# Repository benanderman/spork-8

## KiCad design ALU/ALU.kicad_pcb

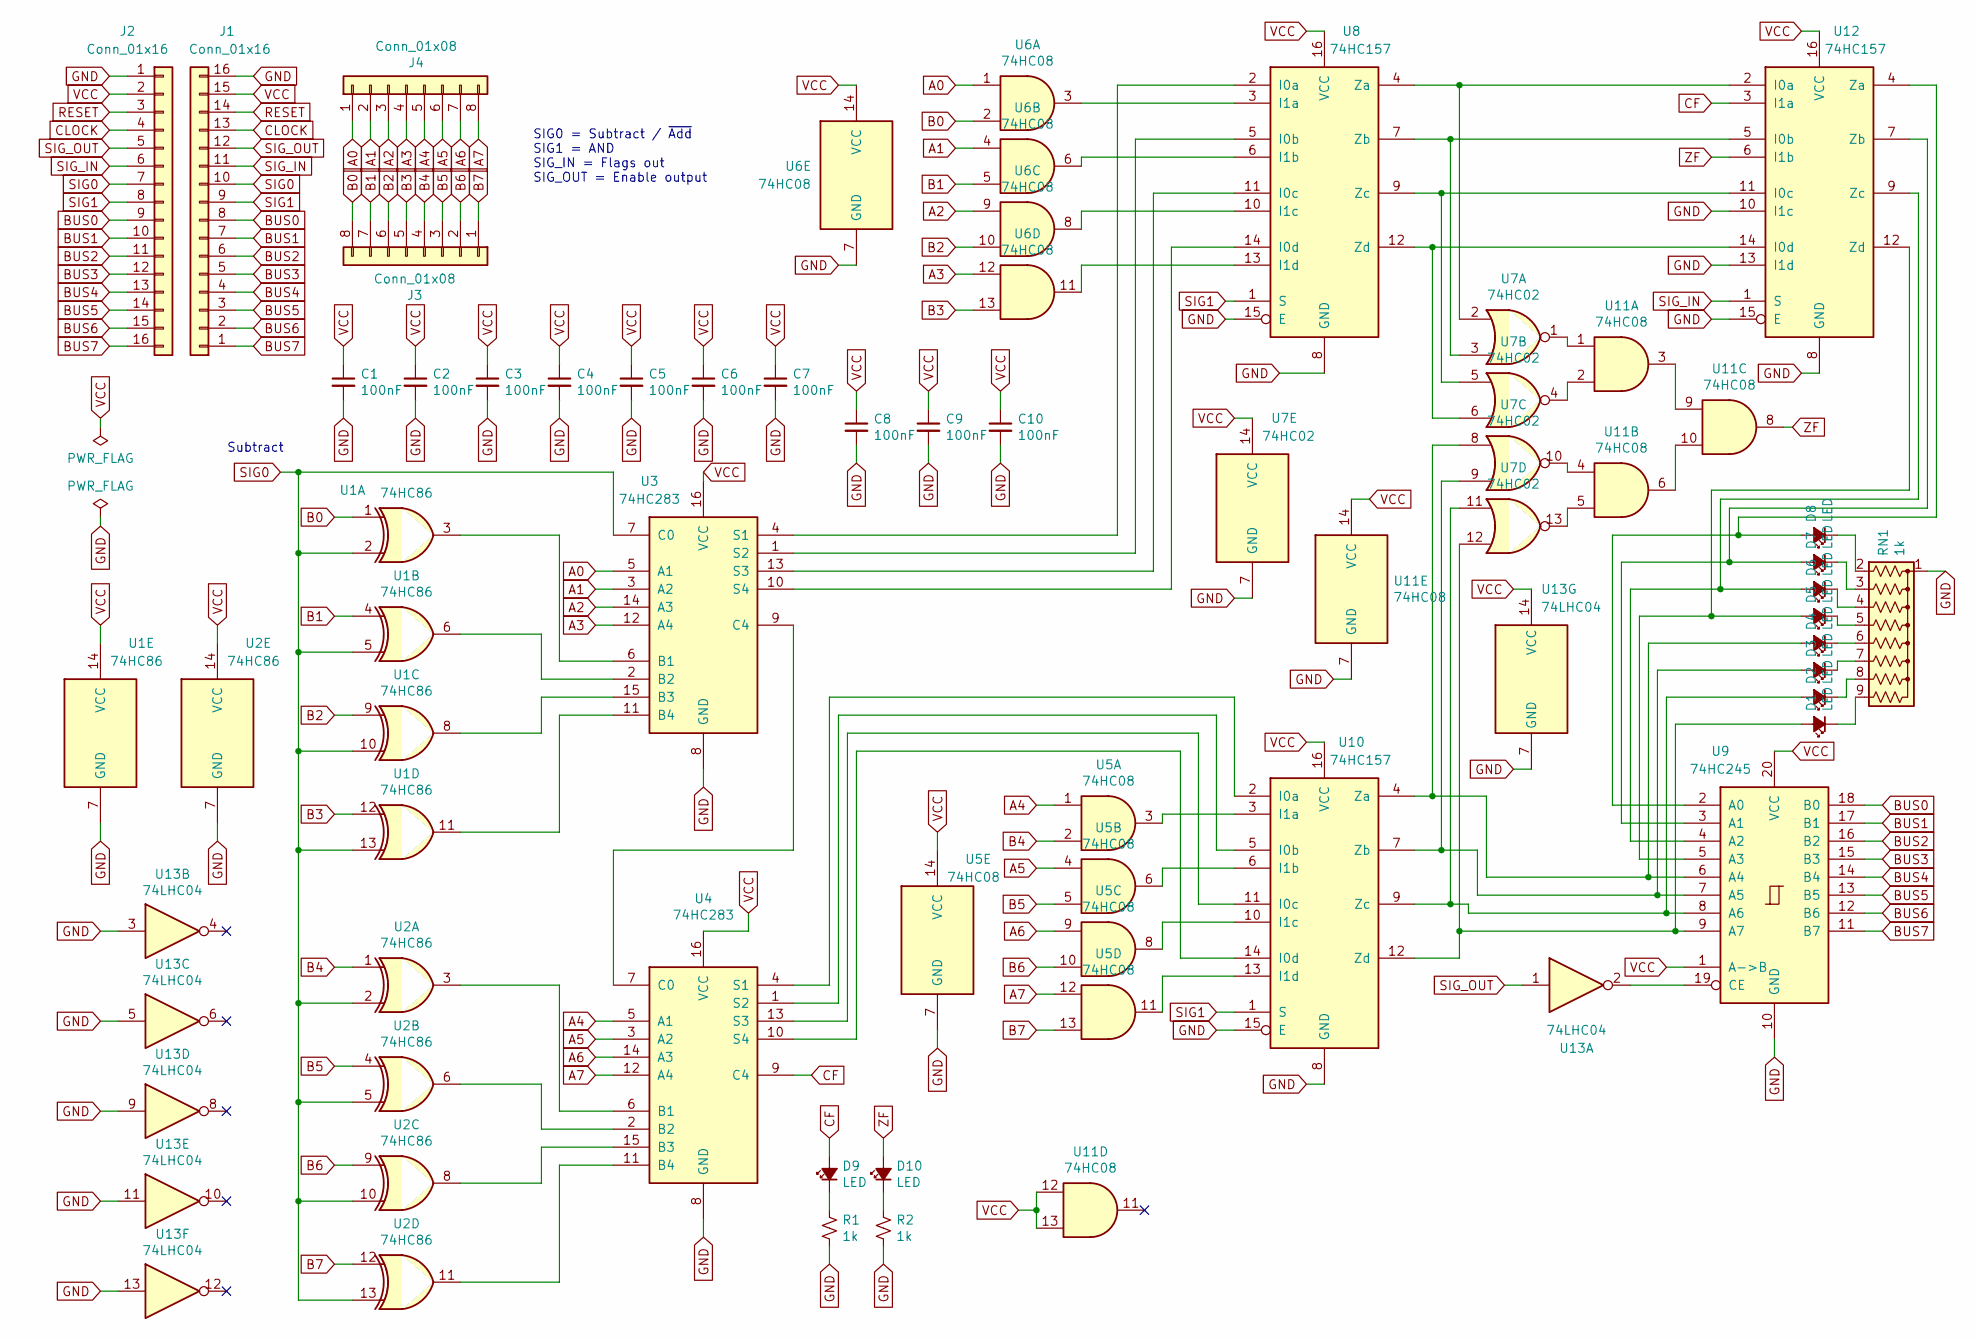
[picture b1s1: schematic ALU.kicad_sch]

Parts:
C1, C2, C3, C4, C5, C6, C7, C8, C9, C10: 100nF; C_Disc_D4.3mm_W1.9mm_P5.00mm
D1, D2, D3, D4, D5, D6, D7, D8, D9, D10: LED; LED_D3.0mm_Clear
J1, J2: Conn_01x16; PinHeader_1x16_P2.54mm_Horizontal
J3, J4: Conn_01x08; PinHeader_1x08_P2.54mm_Horizontal
R1, R2: 1k; R_Axial_DIN0207_L6.3mm_D2.5mm_P7.62mm_Horizontal
RN1: 1k; R_Array_SIP9
U1, U2: 74HC86; DIP-14_W7.62mm
U3, U4: 74HC283; DIP-16_W7.62mm
U5, U6, U11: 74HC08; DIP-14_W7.62mm
U7: 74HC02; DIP-14_W7.62mm
U8, U10, U12: 74HC157; DIP-16_W7.62mm
U9: 74HC245; DIP-20_W7.62mm
U13: 74LHC04; DIP-14_W7.62mm

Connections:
A0: J4.1, U3.5 (A1), U6.1
A1: J4.2, U3.3 (A2), U6.4
A2: J4.3, U3.14 (A3), U6.9
A3: J4.4, U3.12 (A4), U6.12
A4: J4.5, U4.5 (A1), U5.1
A5: J4.6, U4.3 (A2), U5.4
A6: J4.7, U4.14 (A3), U5.9
A7: J4.8, U4.12 (A4), U5.12
B0: J3.8, U1.1, U6.2
B1: J3.7, U1.4, U6.5
B2: J3.6, U1.9, U6.10
B3: J3.5, U1.12, U6.13
B4: J3.4, U2.1, U5.2
B5: J3.3, U2.4, U5.5
B6: J3.2, U2.9, U5.10
B7: J3.1, U2.12, U5.13
BUS0: J1.8, J2.9, U9.18 (B0)
BUS1: J1.7, J2.10, U9.17 (B1)
BUS2: J1.6, J2.11, U9.16 (B2)
BUS3: J1.5, J2.12, U9.15 (B3)
BUS4: J1.4, J2.13, U9.14 (B4)
BUS5: J1.3, J2.14, U9.13 (B5)
BUS6: J1.2, J2.15, U9.12 (B6)
BUS7: J1.1, J2.16, U9.11 (B7)
CF: D9.2 (A), U4.9 (C4), U12.3 (I1a)
CLOCK: J1.13, J2.4
GND: C1.2, C2.2, C3.2, C4.2, C5.2, C6.2, C7.2, C8.2, C9.2, C10.2, J1.16, J2.1, R1.2, R2.2, RN1.1 (common), U1.7 (GND), U2.7 (GND), U3.8 (GND), U4.8 (GND), U5.7 (GND), U6.7 (GND), U7.7 (GND), U8.8 (GND), U8.15 (E), U9.10 (GND), U10.8 (GND), U10.15 (E), U11.7 (GND), U12.8 (GND), U12.10 (I1c), U12.13 (I1d), U12.15 (E), U13.3, U13.5, U13.7 (GND), U13.9, U13.11, U13.13
unnamed: D1.2 (A), U7.12, U9.9 (A7), U10.12 (Zd)
unnamed: D1.1 (K), RN1.9 (R8)
unnamed: D2.2 (A), U7.11, U9.8 (A6), U10.9 (Zc)
unnamed: D2.1 (K), RN1.8 (R7)
unnamed: D3.2 (A), U7.9, U9.7 (A5), U10.7 (Zb)
unnamed: D3.1 (K), RN1.7 (R6)
unnamed: D4.2 (A), U7.8, U9.6 (A4), U10.4 (Za)
unnamed: D4.1 (K), RN1.6 (R5)
unnamed: D5.2 (A), U9.5 (A3), U12.12 (Zd)
unnamed: D5.1 (K), RN1.5 (R4)
unnamed: D6.2 (A), U9.4 (A2), U12.9 (Zc)
unnamed: D6.1 (K), RN1.4 (R3)
unnamed: D7.2 (A), U9.3 (A1), U12.7 (Zb)
unnamed: D7.1 (K), RN1.3 (R2)
unnamed: D8.2 (A), U9.2 (A0), U12.4 (Za)
unnamed: D8.1 (K), RN1.2 (R1)
unnamed: D9.1 (K), R1.1
unnamed: D10.1 (K), R2.1
unnamed: U1.3, U3.6 (B1)
unnamed: U1.6, U3.2 (B2)
unnamed: U1.8, U3.15 (B3)
unnamed: U1.11, U3.11 (B4)
unnamed: U3.9 (C4), U4.7 (C0)
unnamed: U3.4 (S1), U8.2 (I0a)
unnamed: U3.1 (S2), U8.5 (I0b)
unnamed: U3.13 (S3), U8.11 (I0c)
unnamed: U3.10 (S4), U8.14 (I0d)
unnamed: U2.3, U4.6 (B1)
unnamed: U2.6, U4.2 (B2)
unnamed: U2.8, U4.15 (B3)
unnamed: U2.11, U4.11 (B4)
unnamed: U6.3, U8.3 (I1a)
unnamed: U6.6, U8.6 (I1b)
unnamed: U6.8, U8.10 (I1c)
unnamed: U6.11, U8.13 (I1d)
unnamed: U9.19 (CE), U13.2
unnamed: U4.4 (S1), U10.2 (I0a)
unnamed: U4.1 (S2), U10.5 (I0b)
unnamed: U4.13 (S3), U10.11 (I0c)
unnamed: U4.10 (S4), U10.14 (I0d)
unnamed: U5.3, U10.3 (I1a)
unnamed: U5.6, U10.6 (I1b)
unnamed: U5.8, U10.10 (I1c)
unnamed: U5.11, U10.13 (I1d)
unnamed: U7.1, U11.1
unnamed: U7.4, U11.2
unnamed: U11.3, U11.9
unnamed: U7.10, U11.4
unnamed: U7.13, U11.5
unnamed: U11.6, U11.10
unnamed: U7.2, U8.4 (Za), U12.2 (I0a)
unnamed: U7.3, U8.7 (Zb), U12.5 (I0b)
unnamed: U7.5, U8.9 (Zc), U12.11 (I0c)
unnamed: U7.6, U8.12 (Zd), U12.14 (I0d)
RESET: J1.14, J2.3
SIG0: J1.10, J2.7, U1.2, U1.5, U1.10, U1.13, U2.2, U2.5, U2.10, U2.13, U3.7 (C0)
SIG1: J1.9, J2.8, U8.1 (S), U10.1 (S)
SIG_IN: J1.11, J2.6, U12.1 (S)
SIG_OUT: J1.12, J2.5, U13.1
VCC: C1.1, C2.1, C3.1, C4.1, C5.1, C6.1, C7.1, C8.1, C9.1, C10.1, J1.15, J2.2, U1.14 (VCC), U2.14 (VCC), U3.16 (VCC), U4.16 (VCC), U5.14 (VCC), U6.14 (VCC), U7.14 (VCC), U8.16 (VCC), U9.1 (A->B), U9.20 (VCC), U10.16 (VCC), U11.12, U11.13, U11.14 (VCC), U12.16 (VCC), U13.14 (VCC)
ZF: D10.2 (A), U11.8, U12.6 (I1b)

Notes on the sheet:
Subtract
SIG0 = Subtract / ~{Add} SIG1 = AND SIG_IN = Flags out SIG_OUT = Enable output

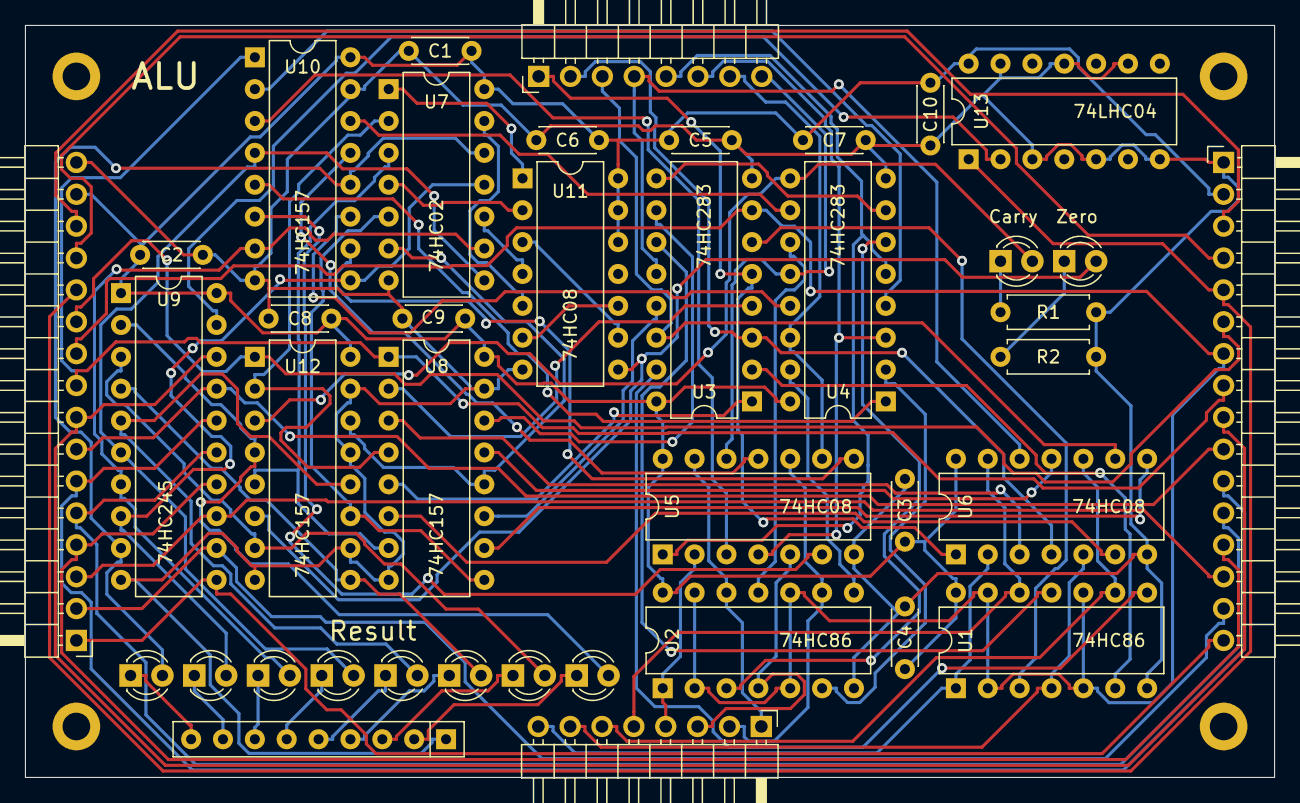
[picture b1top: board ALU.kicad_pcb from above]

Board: 2 copper layers, 99.6 x 59.9 mm, 44 parts (0 on the bottom side), 88 nets.

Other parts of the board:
HOLE1, HOLE2, HOLE3, HOLE4: MountingHole_2.2mm_M2_DIN965_Pad

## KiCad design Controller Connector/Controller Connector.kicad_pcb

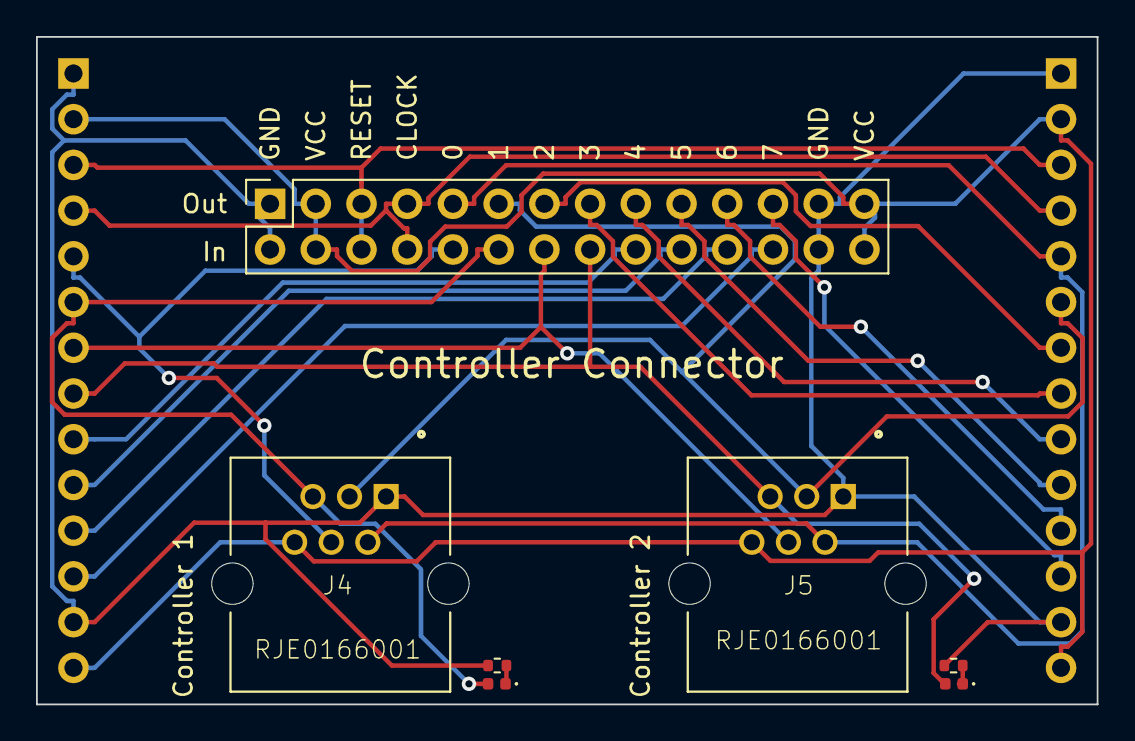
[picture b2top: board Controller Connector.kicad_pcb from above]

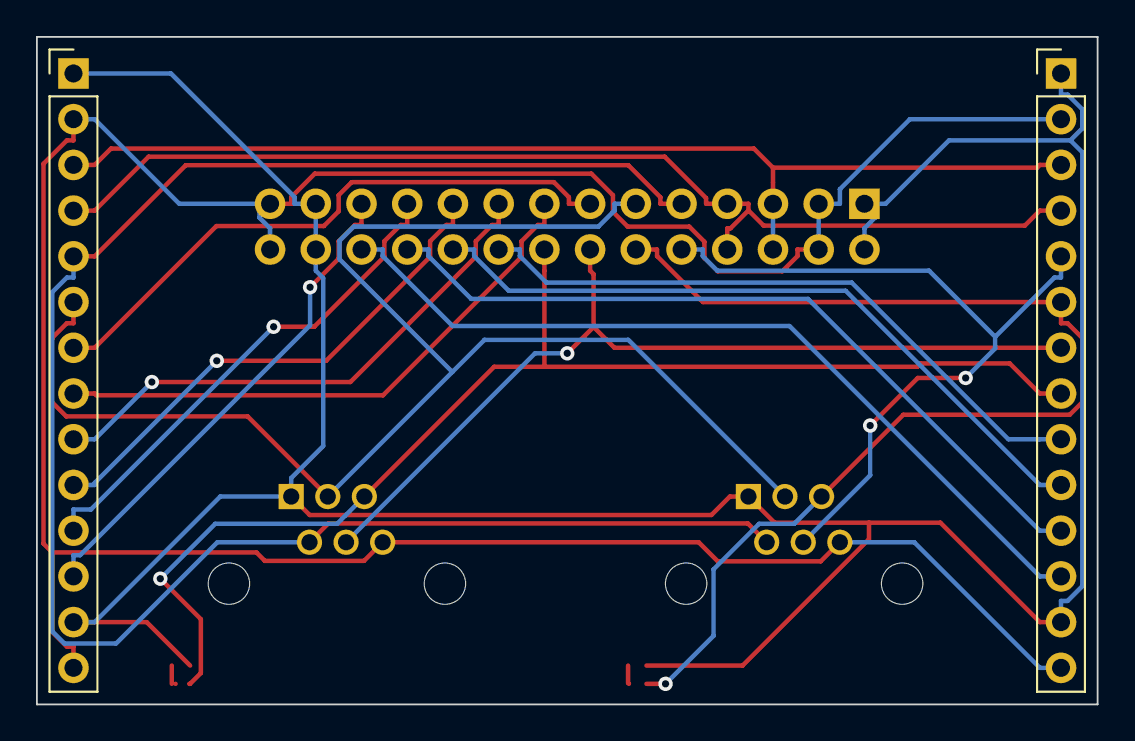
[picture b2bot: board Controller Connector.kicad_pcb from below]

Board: 2 copper layers, 58.9 x 37.1 mm, 9 parts (2 on the bottom side), 22 nets.

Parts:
D1, D2: LED; LED_0402_1005Metric
J1, J2: Conn_01x14; PinHeader_1x14_P2.54mm_Vertical
J3: Conn_02x14_Top_Bottom; PinSocket_2x14_P2.54mm_Vertical
J4, J5: RJE0166001; Connfly_RJ12_DS1133-S60BPX
R1, R2: 10k; R_0402_1005Metric

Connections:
CLOCK: J1.4, J2.4, J3.7, J3.8
GND: J1.1, J1.13, J2.1, J2.13, J3.1, J3.2, J3.25, J3.26, J4.1, J5.1, R1.2, R2.2
IN0: J2.5, J3.10, J4.4
IN1: D1.2 (A), J2.6, J3.12, J4.5
IN2: J2.7, J3.14, J5.4
IN3: D2.2 (A), J2.8, J3.16, J5.5
IN4: J2.9, J3.18
IN5: J2.10, J3.20
IN6: J2.11, J3.22
IN7: J2.12, J3.24
unnamed: D1.1 (K), R1.1
unnamed: D2.1 (K), R2.1
OUT0: J1.5, J3.9, J4.2, J5.2
OUT1: J1.6, J3.11, J4.3, J5.3
OUT2: J1.7, J3.13
OUT3: J1.8, J3.15
OUT4: J1.9, J3.17
OUT5: J1.10, J3.19
OUT6: J1.11, J3.21
OUT7: J1.12, J3.23
RESET: J1.3, J2.3, J3.5, J3.6
VCC: J1.2, J1.14, J2.2, J2.14, J3.3, J3.4, J3.27, J3.28, J4.6, J5.6

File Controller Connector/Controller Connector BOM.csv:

Designator,Comment,Footprint,LCSC Part Number
"D1, D2",LED,LED_0402_1005Metric,C965793
"J1, J2",Conn_01x14,Connector_Generic:Conn_01x14,
J3,Conn_02x14_Top_Bottom,Connector_Generic:Conn_02x14_Odd_Even,
"J4, J5",RJE0166001,RJE0166001-RJE0166001,C77859
"R1, R2",10k,R_0402_1005Metric,C25744

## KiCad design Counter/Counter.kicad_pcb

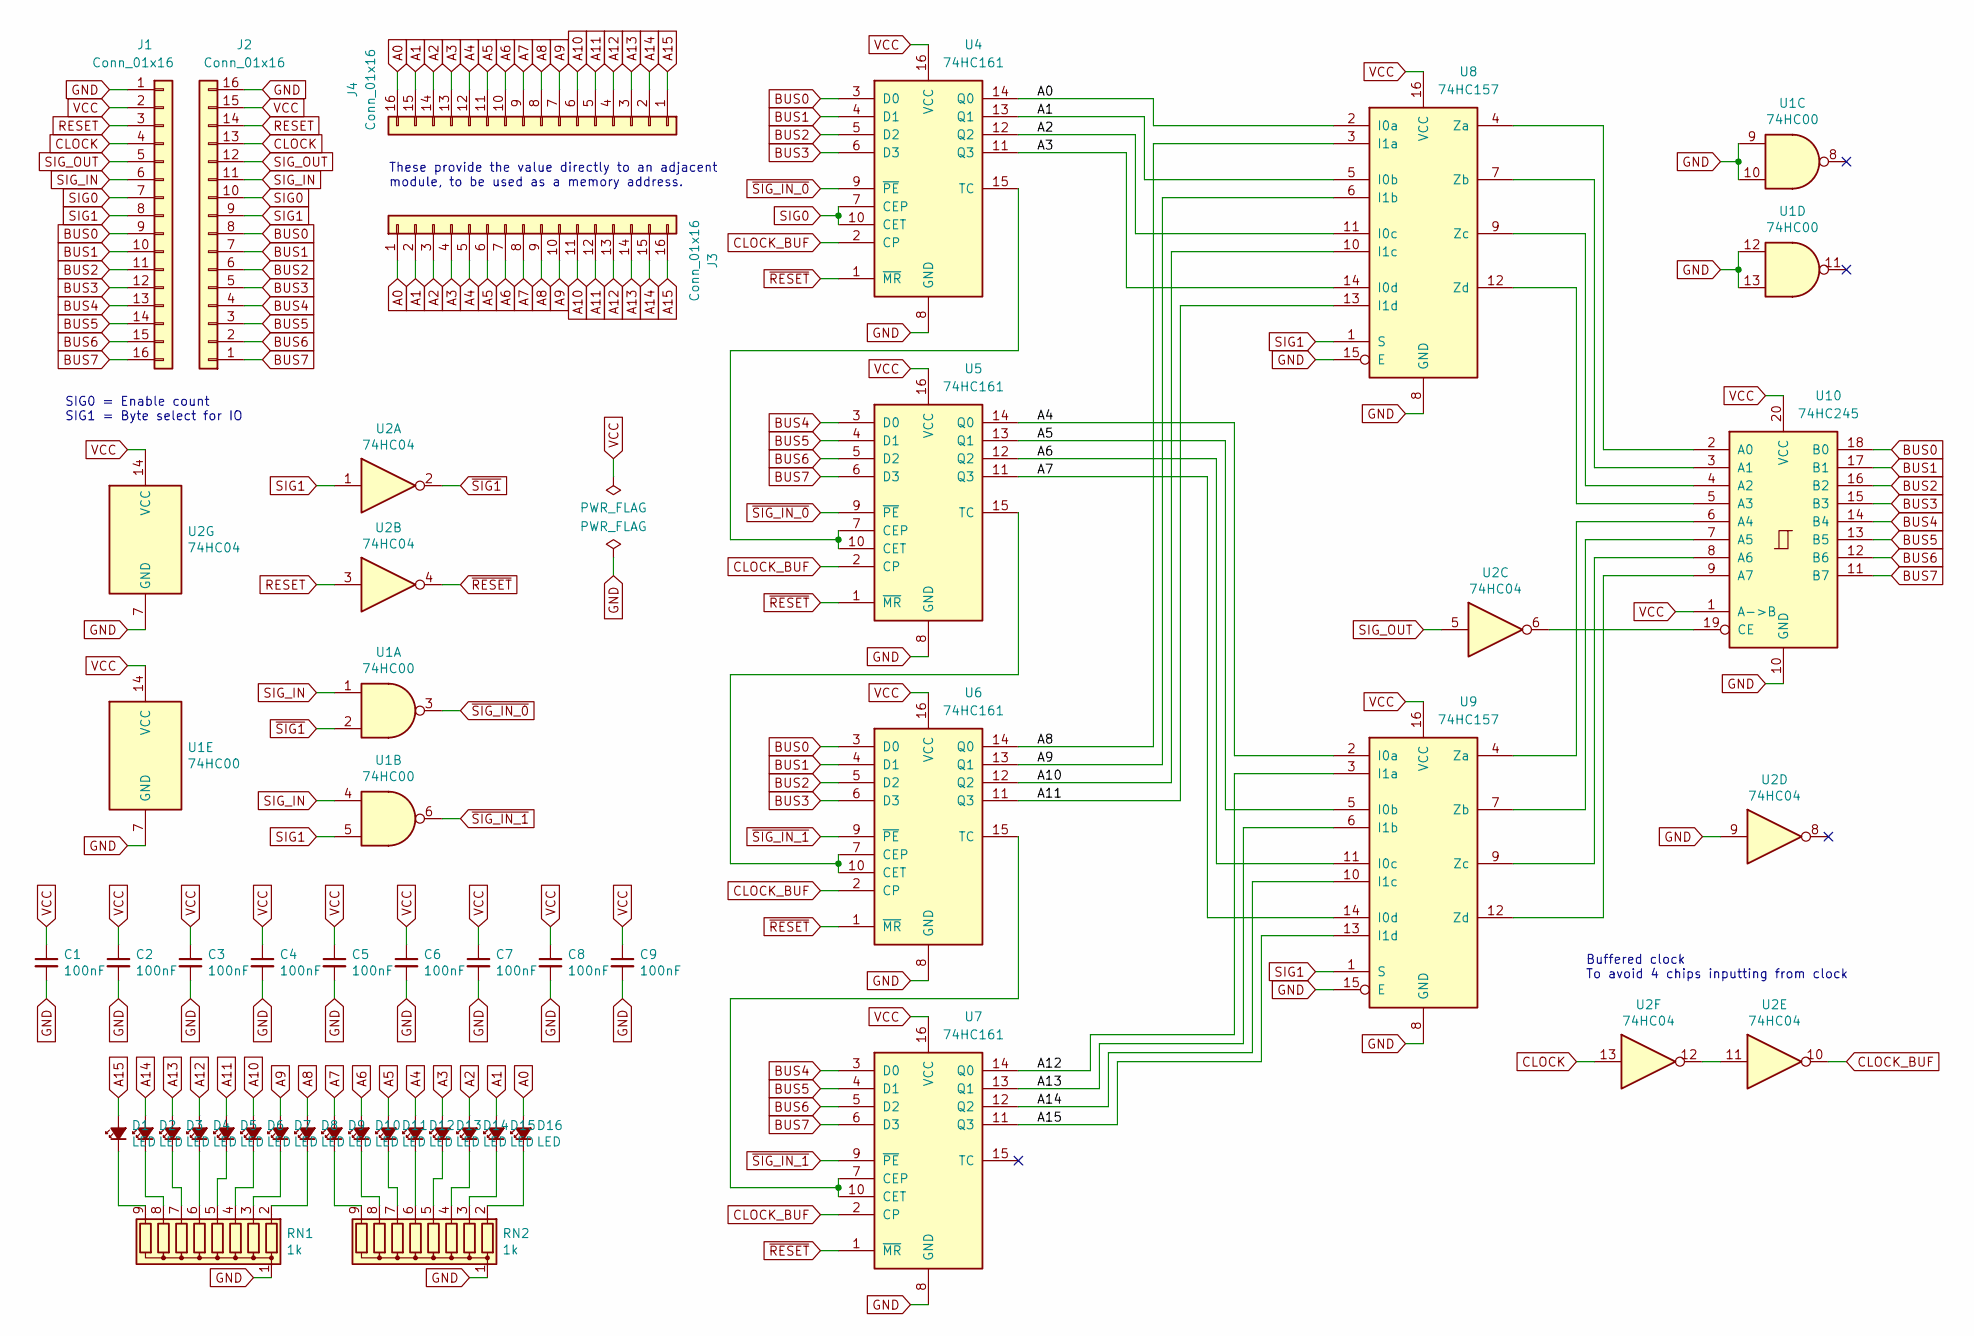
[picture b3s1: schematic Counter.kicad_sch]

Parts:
C1, C2, C3, C4, C5, C6, C7, C8, C9: 100nF; C_Disc_D4.3mm_W1.9mm_P5.00mm
D1, D2, D3, D4, D5, D6, D7, D8, D9, D10, D11, D12, D13, D14, D15, D16: LED; LED_D3.0mm
J1, J2: Conn_01x16; PinHeader_1x16_P2.54mm_Horizontal
J3, J4: Conn_01x16; PinSocket_1x16_P2.54mm_Horizontal
RN1, RN2: 1k; R_Array_SIP9
U1: 74HC00; DIP-14_W7.62mm
U2: 74HC04; DIP-14_W7.62mm
U4, U5, U6, U7: 74HC161; DIP-16_W7.62mm
U8, U9: 74HC157; DIP-16_W7.62mm
U10: 74HC245; DIP-20_W7.62mm

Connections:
A0: D16.2 (A), J3.1, J4.16, U4.14 (Q0), U8.2 (I0a)
A1: D15.2 (A), J3.2, J4.15, U4.13 (Q1), U8.5 (I0b)
A2: D14.2 (A), J3.3, J4.14, U4.12 (Q2), U8.11 (I0c)
A3: D13.2 (A), J3.4, J4.13, U4.11 (Q3), U8.14 (I0d)
A4: D12.2 (A), J3.5, J4.12, U5.14 (Q0), U9.2 (I0a)
A5: D11.2 (A), J3.6, J4.11, U5.13 (Q1), U9.5 (I0b)
A6: D10.2 (A), J3.7, J4.10, U5.12 (Q2), U9.11 (I0c)
A7: D9.2 (A), J3.8, J4.9, U5.11 (Q3), U9.14 (I0d)
A8: D8.2 (A), J3.9, J4.8, U6.14 (Q0), U8.3 (I1a)
A9: D7.2 (A), J3.10, J4.7, U6.13 (Q1), U8.6 (I1b)
A10: D6.2 (A), J3.11, J4.6, U6.12 (Q2), U8.10 (I1c)
A11: D5.2 (A), J3.12, J4.5, U6.11 (Q3), U8.13 (I1d)
A12: D4.2 (A), J3.13, J4.4, U7.14 (Q0), U9.3 (I1a)
A13: D3.2 (A), J3.14, J4.3, U7.13 (Q1), U9.6 (I1b)
A14: D2.2 (A), J3.15, J4.2, U7.12 (Q2), U9.10 (I1c)
A15: D1.2 (A), J3.16, J4.1, U7.11 (Q3), U9.13 (I1d)
BUS0: J1.9, J2.8, U4.3 (D0), U6.3 (D0), U10.18 (B0)
BUS1: J1.10, J2.7, U4.4 (D1), U6.4 (D1), U10.17 (B1)
BUS2: J1.11, J2.6, U4.5 (D2), U6.5 (D2), U10.16 (B2)
BUS3: J1.12, J2.5, U4.6 (D3), U6.6 (D3), U10.15 (B3)
BUS4: J1.13, J2.4, U5.3 (D0), U7.3 (D0), U10.14 (B4)
BUS5: J1.14, J2.3, U5.4 (D1), U7.4 (D1), U10.13 (B5)
BUS6: J1.15, J2.2, U5.5 (D2), U7.5 (D2), U10.12 (B6)
BUS7: J1.16, J2.1, U5.6 (D3), U7.6 (D3), U10.11 (B7)
CLOCK: J1.4, J2.13, U2.13
CLOCK_BUF: U2.10, U4.2 (CP), U5.2 (CP), U6.2 (CP), U7.2 (CP)
GND: C1.2, C2.2, C3.2, C4.2, C5.2, C6.2, C7.2, C8.2, C9.2, J1.1, J2.16, RN1.1 (common), RN2.1 (common), U1.7 (GND), U1.9, U1.10, U1.12, U1.13, U2.7 (GND), U2.9, U4.8 (GND), U5.8 (GND), U6.8 (GND), U7.8 (GND), U8.8 (GND), U8.15 (E), U9.8 (GND), U9.15 (E), U10.10 (GND)
unnamed: D1.1 (K), RN1.9 (R8)
unnamed: D2.1 (K), RN1.8 (R7)
unnamed: D3.1 (K), RN1.7 (R6)
unnamed: D4.1 (K), RN1.6 (R5)
unnamed: D5.1 (K), RN1.5 (R4)
unnamed: D6.1 (K), RN1.4 (R3)
unnamed: D7.1 (K), RN1.3 (R2)
unnamed: D8.1 (K), RN1.2 (R1)
unnamed: D9.1 (K), RN2.9 (R8)
unnamed: D10.1 (K), RN2.8 (R7)
unnamed: D11.1 (K), RN2.7 (R6)
unnamed: D12.1 (K), RN2.6 (R5)
unnamed: D13.1 (K), RN2.5 (R4)
unnamed: D14.1 (K), RN2.4 (R3)
unnamed: D15.1 (K), RN2.3 (R2)
unnamed: D16.1 (K), RN2.2 (R1)
unnamed: U2.11, U2.12
unnamed: U4.15 (TC), U5.7 (CEP), U5.10 (CET)
unnamed: U5.15 (TC), U6.7 (CEP), U6.10 (CET)
unnamed: U6.15 (TC), U7.7 (CEP), U7.10 (CET)
unnamed: U8.4 (Za), U10.2 (A0)
unnamed: U8.7 (Zb), U10.3 (A1)
unnamed: U8.9 (Zc), U10.4 (A2)
unnamed: U8.12 (Zd), U10.5 (A3)
unnamed: U9.4 (Za), U10.6 (A4)
unnamed: U9.7 (Zb), U10.7 (A5)
unnamed: U9.9 (Zc), U10.8 (A6)
unnamed: U9.12 (Zd), U10.9 (A7)
unnamed: U2.6, U10.19 (CE)
RESET: J1.3, J2.14, U2.3
SIG0: J1.7, J2.10, U4.7 (CEP), U4.10 (CET)
SIG1: J1.8, J2.9, U1.5, U2.1, U8.1 (S), U9.1 (S)
SIG_IN: J1.6, J2.11, U1.1, U1.4
SIG_OUT: J1.5, J2.12, U2.5
VCC: C1.1, C2.1, C3.1, C4.1, C5.1, C6.1, C7.1, C8.1, C9.1, J1.2, J2.15, U1.14 (VCC), U2.14 (VCC), U4.16 (VCC), U5.16 (VCC), U6.16 (VCC), U7.16 (VCC), U8.16 (VCC), U9.16 (VCC), U10.1 (A->B), U10.20 (VCC)
~RESET: U2.4, U4.1 (~MR), U5.1 (~MR), U6.1 (~MR), U7.1 (~MR)
~SIG1: U1.2, U2.2
~SIG_IN_0: U1.3, U4.9 (~PE), U5.9 (~PE)
~SIG_IN_1: U1.6, U6.9 (~PE), U7.9 (~PE)

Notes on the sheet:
Buffered clock To avoid 4 chips inputting from clock
SIG0 = Enable count SIG1 = Byte select for IO
These provide the value directly to an adjacent module, to be used as a memory address.

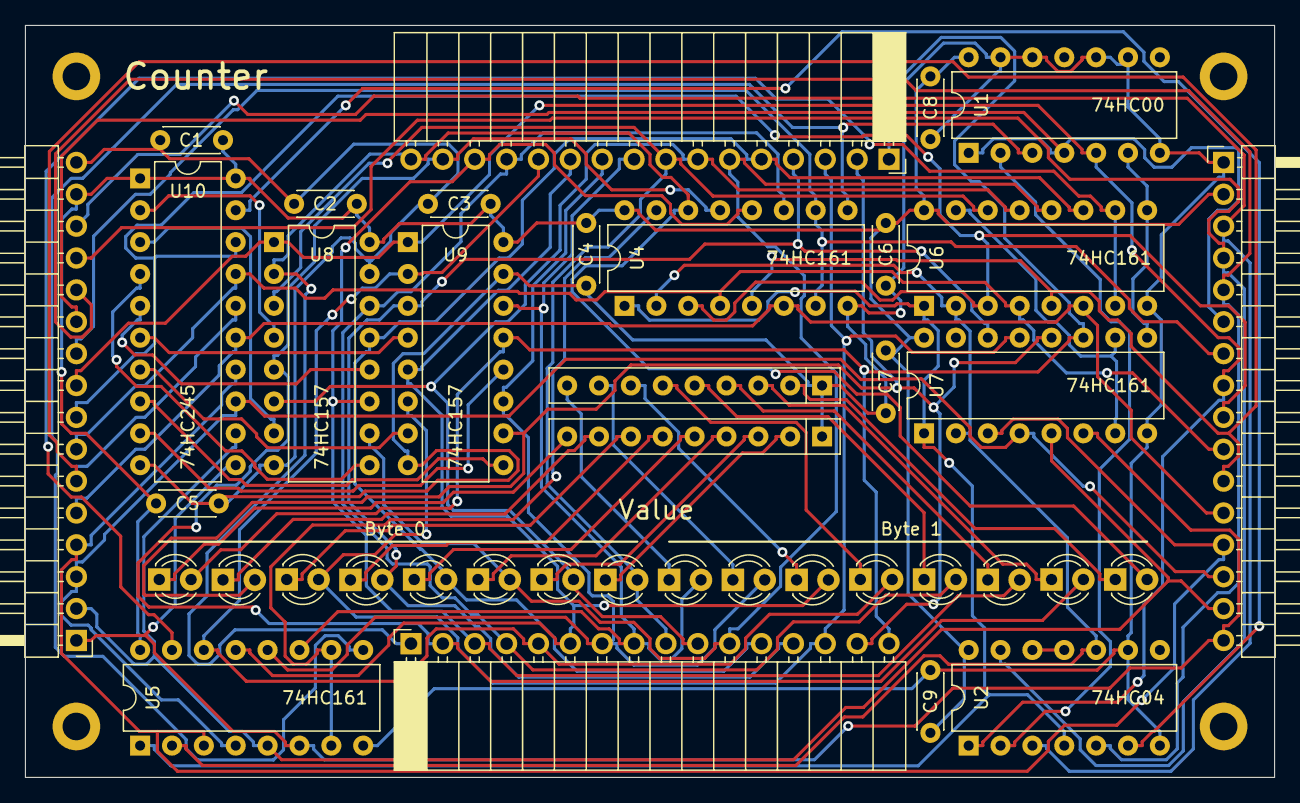
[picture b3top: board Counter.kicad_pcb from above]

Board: 2 copper layers, 99.6 x 59.9 mm, 44 parts (0 on the bottom side), 66 nets.

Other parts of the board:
HOLE1, HOLE2, HOLE3, HOLE4: MountingHole_2.2mm_M2_DIN965_Pad

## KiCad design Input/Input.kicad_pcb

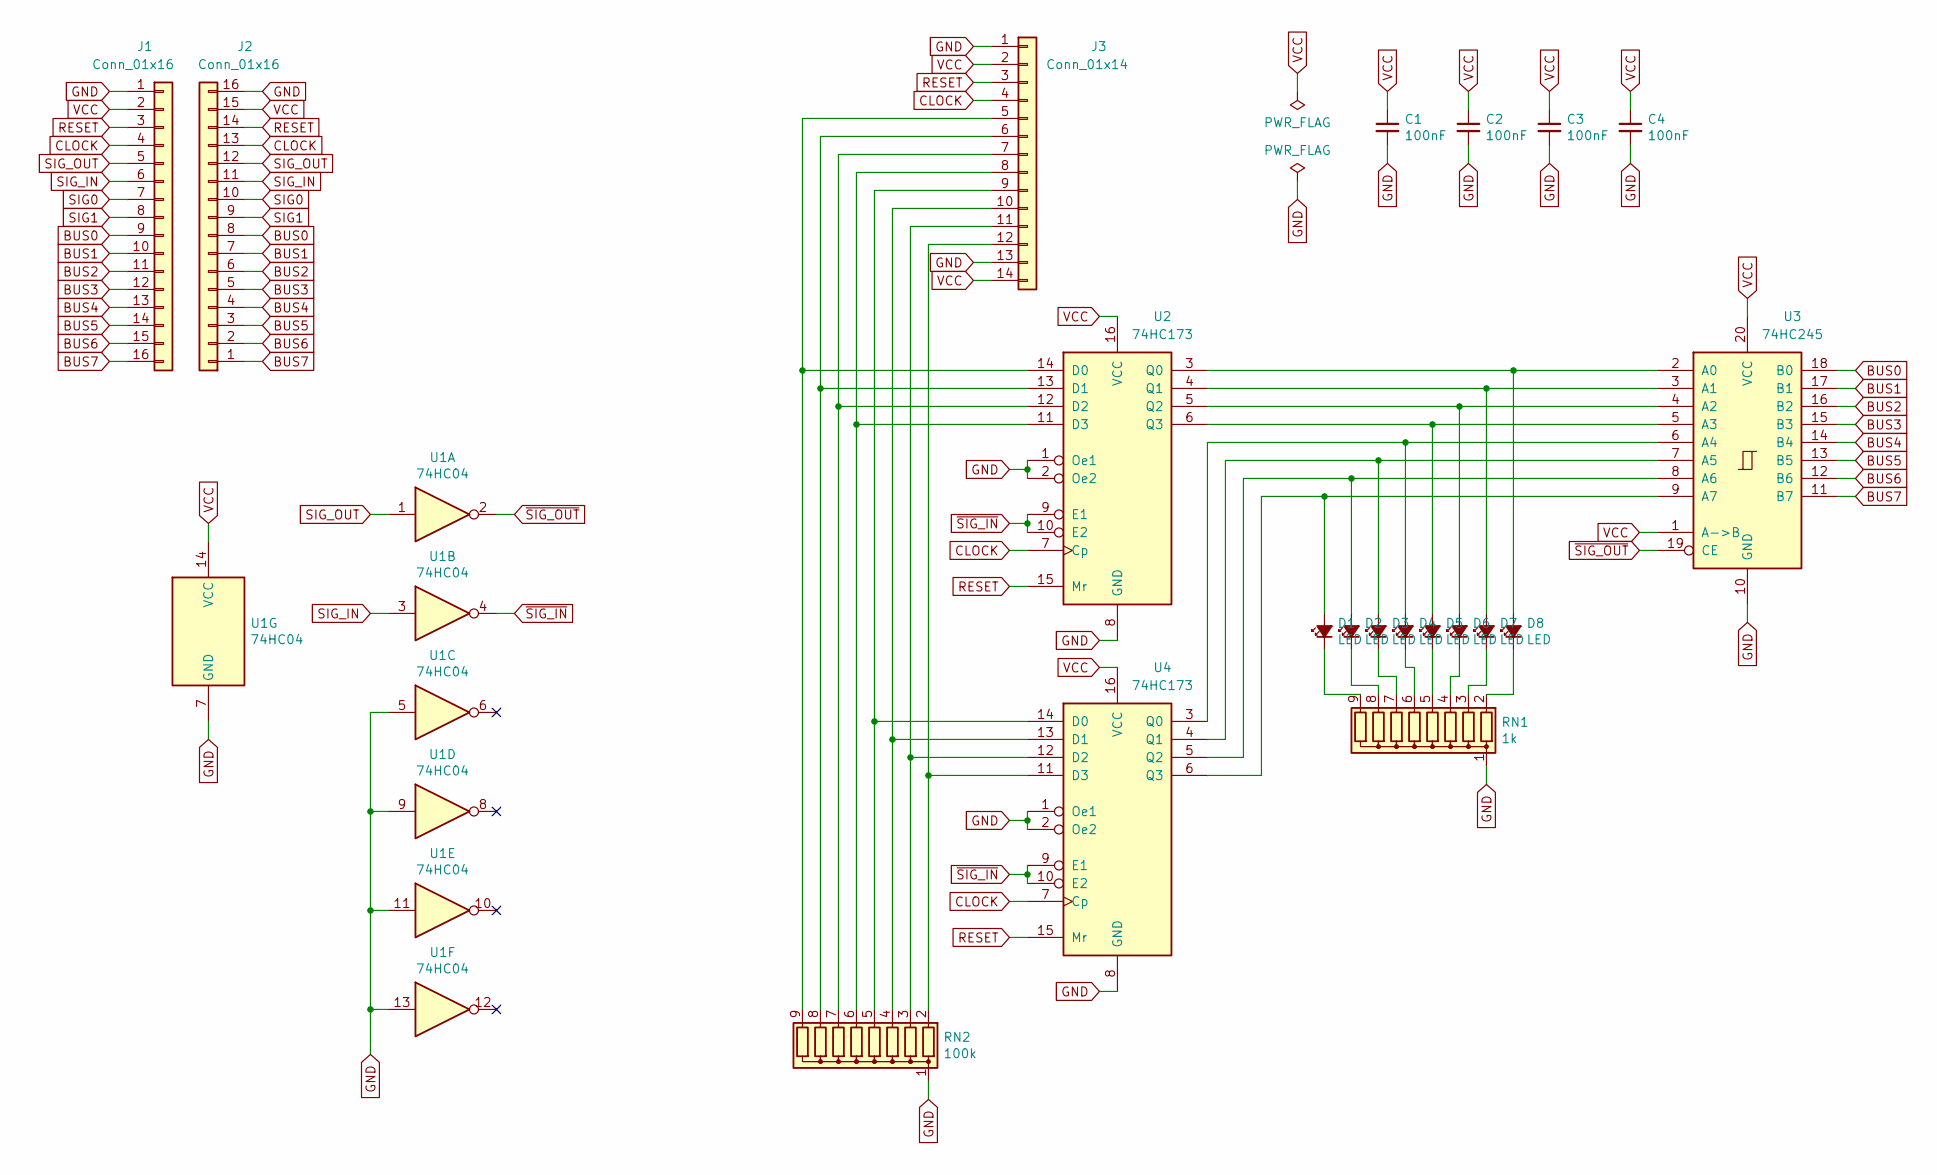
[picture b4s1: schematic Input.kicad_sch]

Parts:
C1, C2, C3, C4: 100nF; C_Disc_D4.3mm_W1.9mm_P5.00mm
D1, D2, D3, D4, D5, D6, D7, D8: LED; LED_D3.0mm_Clear
J1, J2: Conn_01x16; PinHeader_1x16_P2.54mm_Horizontal
J3: Conn_01x14; PinSocket_1x14_P2.54mm_Vertical
RN1: 1k; R_Array_SIP9
RN2: 100k; R_Array_SIP9
U1: 74HC04; DIP-14_W7.62mm
U2, U4: 74HC173; DIP-16_W7.62mm
U3: 74HC245; DIP-20_W7.62mm

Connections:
BUS0: J1.9, J2.8, U3.18 (B0)
BUS1: J1.10, J2.7, U3.17 (B1)
BUS2: J1.11, J2.6, U3.16 (B2)
BUS3: J1.12, J2.5, U3.15 (B3)
BUS4: J1.13, J2.4, U3.14 (B4)
BUS5: J1.14, J2.3, U3.13 (B5)
BUS6: J1.15, J2.2, U3.12 (B6)
BUS7: J1.16, J2.1, U3.11 (B7)
CLOCK: J1.4, J2.13, J3.4, U2.7 (Cp), U4.7 (Cp)
GND: C1.2, C2.2, C3.2, C4.2, J1.1, J2.16, J3.1, J3.13, RN1.1 (common), RN2.1 (common), U1.5, U1.7 (GND), U1.9, U1.11, U1.13, U2.1 (Oe1), U2.2 (Oe2), U2.8 (GND), U3.10 (GND), U4.1 (Oe1), U4.2 (Oe2), U4.8 (GND)
unnamed: D1.2 (A), U3.9 (A7), U4.6 (Q3)
unnamed: D1.1 (K), RN1.9 (R8)
unnamed: D2.2 (A), U3.8 (A6), U4.5 (Q2)
unnamed: D2.1 (K), RN1.8 (R7)
unnamed: D3.2 (A), U3.7 (A5), U4.4 (Q1)
unnamed: D3.1 (K), RN1.7 (R6)
unnamed: D4.2 (A), U3.6 (A4), U4.3 (Q0)
unnamed: D4.1 (K), RN1.6 (R5)
unnamed: D5.2 (A), U2.6 (Q3), U3.5 (A3)
unnamed: D5.1 (K), RN1.5 (R4)
unnamed: D6.2 (A), U2.5 (Q2), U3.4 (A2)
unnamed: D6.1 (K), RN1.4 (R3)
unnamed: D7.2 (A), U2.4 (Q1), U3.3 (A1)
unnamed: D7.1 (K), RN1.3 (R2)
unnamed: D8.2 (A), U2.3 (Q0), U3.2 (A0)
unnamed: D8.1 (K), RN1.2 (R1)
unnamed: J3.5, RN2.9 (R8), U2.14 (D0)
unnamed: J3.6, RN2.8 (R7), U2.13 (D1)
unnamed: J3.7, RN2.7 (R6), U2.12 (D2)
unnamed: J3.8, RN2.6 (R5), U2.11 (D3)
unnamed: J3.9, RN2.5 (R4), U4.14 (D0)
unnamed: J3.10, RN2.4 (R3), U4.13 (D1)
unnamed: J3.11, RN2.3 (R2), U4.12 (D2)
unnamed: J3.12, RN2.2 (R1), U4.11 (D3)
RESET: J1.3, J2.14, J3.3, U2.15 (Mr), U4.15 (Mr)
SIG0: J1.7, J2.10
SIG1: J1.8, J2.9
SIG_IN: J1.6, J2.11, U1.3
SIG_OUT: J1.5, J2.12, U1.1
VCC: C1.1, C2.1, C3.1, C4.1, J1.2, J2.15, J3.2, J3.14, U1.14 (VCC), U2.16 (VCC), U3.1 (A->B), U3.20 (VCC), U4.16 (VCC)
~SIG_IN: U1.4, U2.9 (E1), U2.10 (E2), U4.9 (E1), U4.10 (E2)
~SIG_OUT: U1.2, U3.19 (CE)

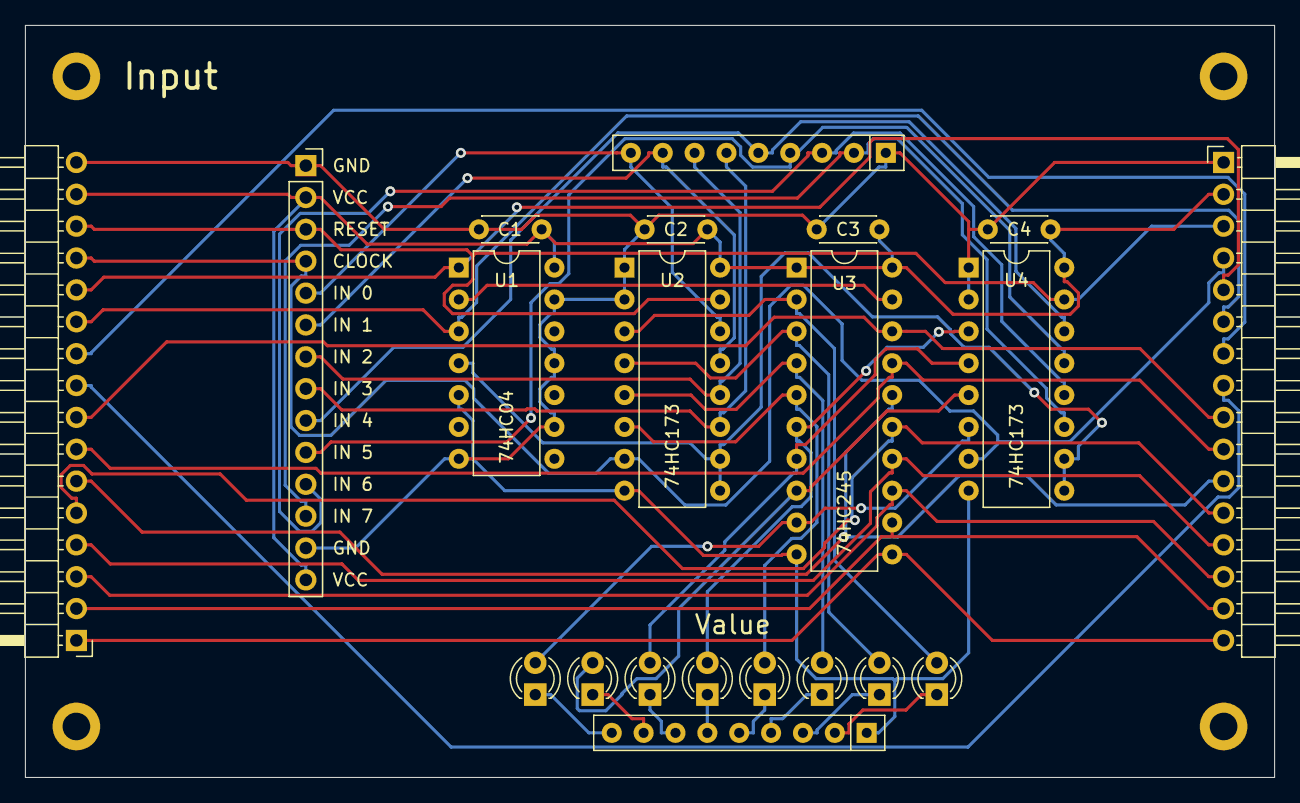
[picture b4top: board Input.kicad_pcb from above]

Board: 2 copper layers, 99.6 x 59.9 mm, 25 parts (0 on the bottom side), 42 nets.

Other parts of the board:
HOLE1, HOLE2, HOLE3, HOLE4: MountingHole_2.2mm_M2_DIN965_Pad

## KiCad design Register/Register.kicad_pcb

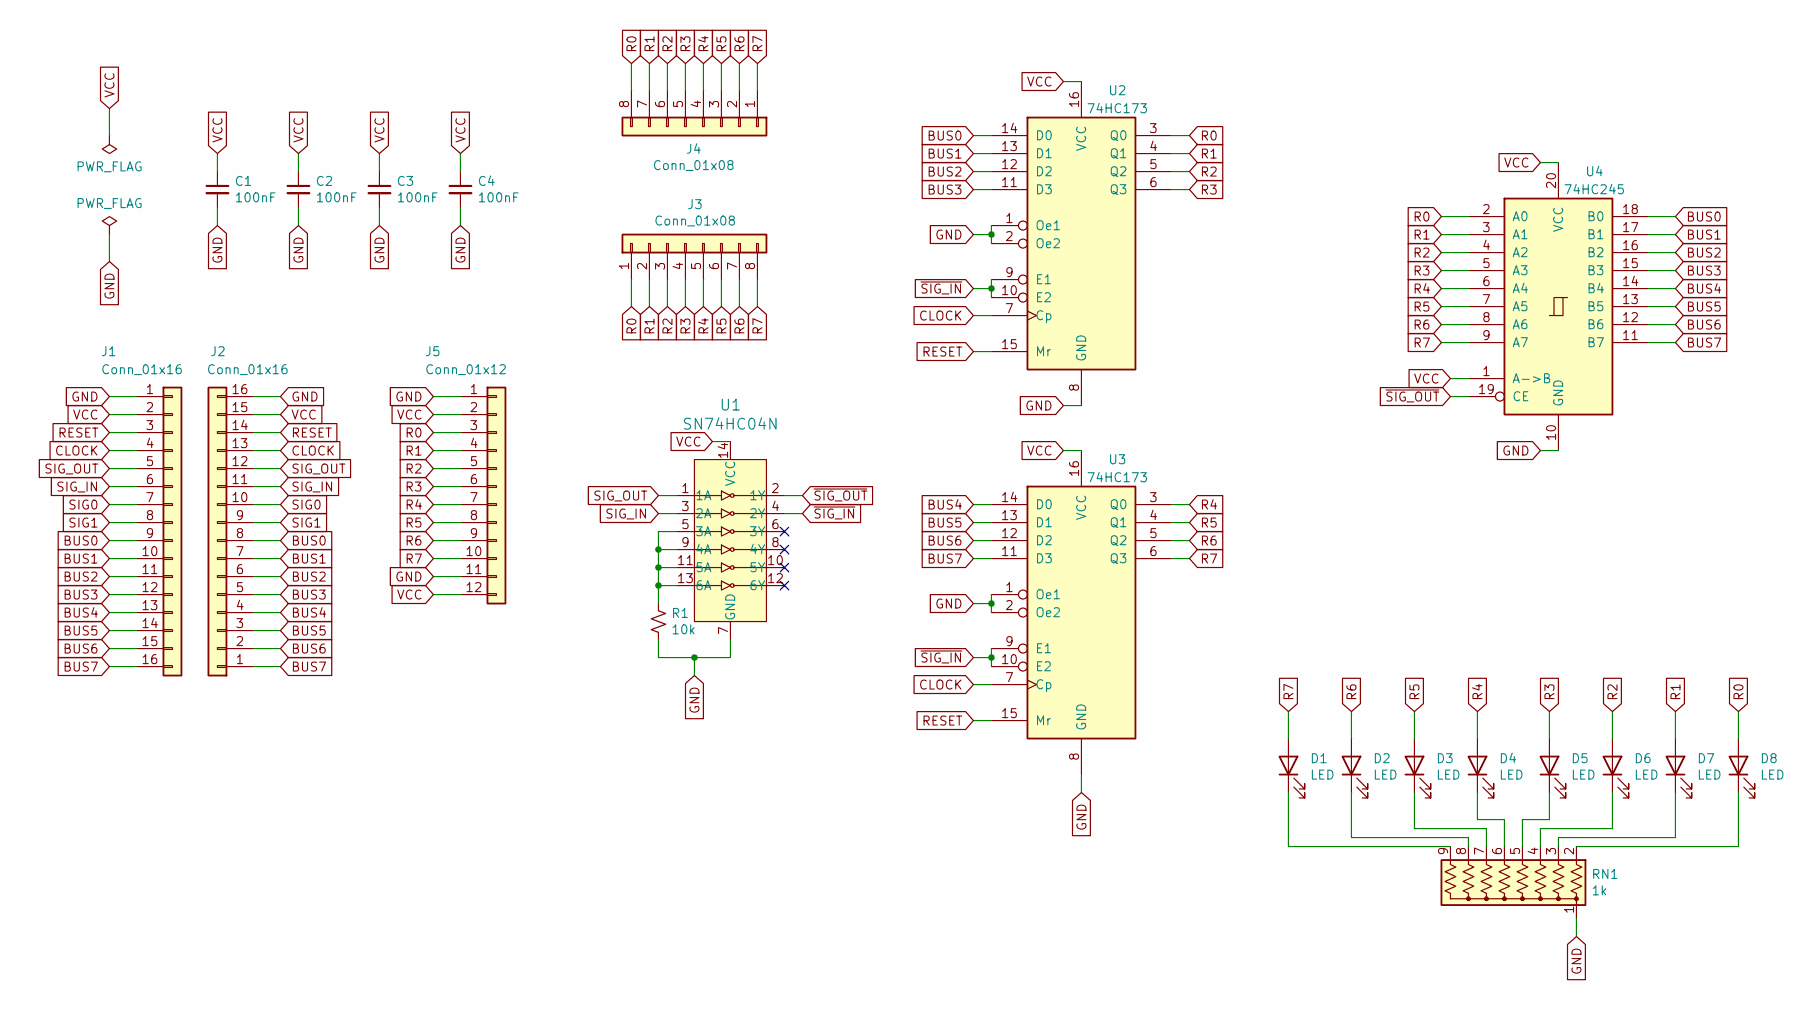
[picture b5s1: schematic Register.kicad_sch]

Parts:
C1, C2, C3, C4: 100nF; C_Disc_D4.3mm_W1.9mm_P5.00mm
D1, D2, D3, D4, D5, D6, D7, D8: LED; LED_D3.0mm_Clear
J1, J2: Conn_01x16; PinHeader_1x16_P2.54mm_Horizontal
J3, J4: Conn_01x08; PinSocket_1x08_P2.54mm_Horizontal
J5: Conn_01x12; PinSocket_1x12_P2.54mm_Vertical
R1: 10k; R_Axial_DIN0207_L6.3mm_D2.5mm_P7.62mm_Horizontal
RN1: 1k; R_Array_SIP9
U1: SN74HC04N; DIP-14_W7.62mm; MPN SN74LS04N; Digi-Key_PN 296-1629-5-ND
U2, U3: 74HC173; DIP-16_W7.62mm
U4: 74HC245; DIP-20_W7.62mm

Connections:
BUS0: J1.9, J2.8, U2.14 (D0), U4.18 (B0)
BUS1: J1.10, J2.7, U2.13 (D1), U4.17 (B1)
BUS2: J1.11, J2.6, U2.12 (D2), U4.16 (B2)
BUS3: J1.12, J2.5, U2.11 (D3), U4.15 (B3)
BUS4: J1.13, J2.4, U3.14 (D0), U4.14 (B4)
BUS5: J1.14, J2.3, U3.13 (D1), U4.13 (B5)
BUS6: J1.15, J2.2, U3.12 (D2), U4.12 (B6)
BUS7: J1.16, J2.1, U3.11 (D3), U4.11 (B7)
CLOCK: J1.4, J2.13, U2.7 (Cp), U3.7 (Cp)
GND: C1.2, C2.2, C3.2, C4.2, J1.1, J2.16, J5.1, J5.11, R1.1, RN1.1 (common), U1.7 (GND), U2.1 (Oe1), U2.2 (Oe2), U2.8 (GND), U3.1 (Oe1), U3.2 (Oe2), U3.8 (GND), U4.10 (GND)
unnamed: D1.1 (K), RN1.9 (R8)
unnamed: D2.1 (K), RN1.8 (R7)
unnamed: D3.1 (K), RN1.7 (R6)
unnamed: D4.1 (K), RN1.6 (R5)
unnamed: D5.1 (K), RN1.5 (R4)
unnamed: D6.1 (K), RN1.4 (R3)
unnamed: D7.1 (K), RN1.3 (R2)
unnamed: D8.1 (K), RN1.2 (R1)
unnamed: R1.2, U1.5 (3A), U1.9 (4A), U1.11 (5A), U1.13 (6A)
R0: D8.2 (A), J3.1, J4.8, J5.3, U2.3 (Q0), U4.2 (A0)
R1: D7.2 (A), J3.2, J4.7, J5.4, U2.4 (Q1), U4.3 (A1)
R2: D6.2 (A), J3.3, J4.6, J5.5, U2.5 (Q2), U4.4 (A2)
R3: D5.2 (A), J3.4, J4.5, J5.6, U2.6 (Q3), U4.5 (A3)
R4: D4.2 (A), J3.5, J4.4, J5.7, U3.3 (Q0), U4.6 (A4)
R5: D3.2 (A), J3.6, J4.3, J5.8, U3.4 (Q1), U4.7 (A5)
R6: D2.2 (A), J3.7, J4.2, J5.9, U3.5 (Q2), U4.8 (A6)
R7: D1.2 (A), J3.8, J4.1, J5.10, U3.6 (Q3), U4.9 (A7)
RESET: J1.3, J2.14, U2.15 (Mr), U3.15 (Mr)
SIG0: J1.7, J2.10
SIG1: J1.8, J2.9
SIG_IN: J1.6, J2.11, U1.3 (2A)
SIG_OUT: J1.5, J2.12, U1.1 (1A)
VCC: C1.1, C2.1, C3.1, C4.1, J1.2, J2.15, J5.2, J5.12, U1.14 (VCC), U2.16 (VCC), U3.16 (VCC), U4.1 (A->B), U4.20 (VCC)
~SIG_IN: U1.4 (2Y), U2.9 (E1), U2.10 (E2), U3.9 (E1), U3.10 (E2)
~SIG_OUT: U1.2 (1Y), U4.19 (CE)
